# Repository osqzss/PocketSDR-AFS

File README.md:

# PocketSDR-AFS

PocketSDR-AFS is an enhanced version of Tomoji Takasu’s [PocketSDR v0.13](https://github.com/tomojitakasu/PocketSDR) designed to support the Augmented Forward Signal (AFS) for the Lunar Augmented Navigation Service (LANS).

LANS is the lunar counterpart to GNSS, developed to enable precise navigation and positioning for future lunar exploration missions. The AFS is a standardized signal structure for LANS. It is transmitted by multiple LunaNet Service Provider (LNSP) nodes, including NASA's Lunar Communications Relay and Navigation Systems (LCRNS), ESA's Moonlight Lunar Communications and Navigation Services (LCNS), and JAXA's Luna Navigation Satellite System (LNSS). The recommended standard for AFS can be found at NASA's [LunaNet Interoperability Specification](https://www.nasa.gov/directorates/somd/space-communications-navigation-program/lunanet-interoperability-specification/) site.

PocketSDR-AFS, in conjunction with a software-defined LANS AFS baseband simulator such as [LANS-AFS-SIM](https://github.com/osqzss/LANS-AFS-SIM), offers a flexible platform for validating LANS signal processing algorithms and evaluating lunar navigation performance.

## Build Instructions

### 1. Install Prerequisite Packages

```sh
sudo apt update
sudo apt install libusb-1.0-0-dev libfftw3-dev
```

### 2. Clone the Repository

```sh
git clone https://github.com/osqzss/PocketSDR-AFS.git
cd PocketSDR-AFS
```

### 3. Install External Library Source Trees

```sh
cd lib
chmod +x clone_lib.sh
./clone_lib.sh
```

### 4. Build the Libraries

```sh
cd build
make
make install
```

### 5. Build the `pocket_trk` Executable

```sh
cd ../../app/pocket_trk
make
```

## Usage

The `pocket_trk.sh` script in `app/pocket_trk` provides example command-line instructions for both offline and real-time testing:

- **Offline Testing:** Process 2-bit I/Q sample data generated by LANS-AFS-SIM.
- **Real-time Testing:** Use with the FE2CH frontend on a desktop PC or Raspberry Pi 5.

### Offline Testing Example

```sh
sudo ./pocket_trk.sh afssim_iq2.bin
```

### Real-time Testing Example (with FE2CH frontend)

```sh
sudo ./pocket_trk.sh
```

## Notes

- For development and testing purposes, the center frequency of the LANS AFS is set to 1575.42MHz. While the actual LANS AFS is transmitted in the S-band, this L-band configuration enables compatibility with the FE2CH frontend device, facilitating convenient real-time testing on desktop PCs or Raspberry Pi devices.
- To configure the receiver for S-band signal acquisition, edit the `src/pocket_sdr.h` file and comment out the `#define DEMO_L1` directive. This modification enables support for the S-band center frequency used by the actual LANS AFS broadcast.

## References

For additional details on the architecture and examples of offline and real-time test results, please refer to our publication:

Sobukawa, R., & Ebinuma, T. (2025). Open-Source Real-Time SDR Platform for Rapid Prototyping of LANS AFS Receiver. Aerospace, 12(7), 620. [https://doi.org/10.3390/aerospace12070620](https://www.mdpi.com/2226-4310/12/7/620)

What about the application of the Solomonoff induction
to the RF sensing of human brain?
https://en.wikipedia.org/wiki/Talk:Solomonoff%27s_theory_of_inductive_inference

If we assume that the algorithmic complexity
of neural processes is relatively small
(you could take a look at the Potapov monography
for some arguments)

As far as I know a lot of neural processes in human brain are electric (or electro-chemistry)
in nature. They have a little power and a small
frequency (~ 1-1000 Hz).
So they emit very low frequency radio waves.

You can detect those radio waves on
small antennas if the impedance of such antennas
is matched. This is basically the citation
from the book on electrodynamics.
I uploaded one such book on Twirpix site.

So you can create a lot of such receivers

microstrip filter to filter very high frequencies
impedance matched microstrip antenna
resistor for noise for oversampling
very fast comparator to sample signal
in a very large array on a chip using
standard CMOS or some sort of full-custom process
(maybe even with some new materials)

BeamForming and large arrays of digital correlators with sub-mm positioning accuracy
could be achived.

so it seems there is no theoretical
obstacles to implement some sort of
RF human brain sensing or even control
if you can implement reverse structure
with array of a large amount of RF amplifiers
with sub-mm beam forming accuracy

BTW I wrote that remark:
https://en.wikipedia.org/wiki/Talk:Solomonoff%27s_theory_of_inductive_inference

What about the application of the Solomonoff induction to the person to person information exchange?

It seems the minimum description length principle could be used to deduce minimum ethics. At least you can compare ethics by the length. What about the following question: how to shoot met-art girl in the dark underground? ~2026-24709-41 (talk) 16:43, 8 June 2026 (UTC)

at least we can ask a question: does russian met-art model from a pic want some money?
and what obstacles do that guess so hard?
why it is so hard to contact her directly?
she lose money, interesting person lose opportunity to make some photos.

also, it seems the economy without coordination primitives based on physics or mathematics
like gold or maybe Bitcoin or maybe some sort of other physical objects or processes
is just a chaos.
Economic calculation based on fiat money is impossible just from scientific methodology
https://en.wikipedia.org/wiki/Talk:Solomonoff%27s_theory_of_inductive_inference

It seems it is proof of the famous Mises calculation argument
https://mises.org/online-book/economic-calculation-socialist-commonwealth

https://transitional-writes.dreamwidth.org/44972.html
Kirill Abramovich
Samara, Russia

and the most important question:
what about the minimal ethics deduced from the MDL principle?
is it exist?

what was the obstacle between russian met-art girls and engineers?

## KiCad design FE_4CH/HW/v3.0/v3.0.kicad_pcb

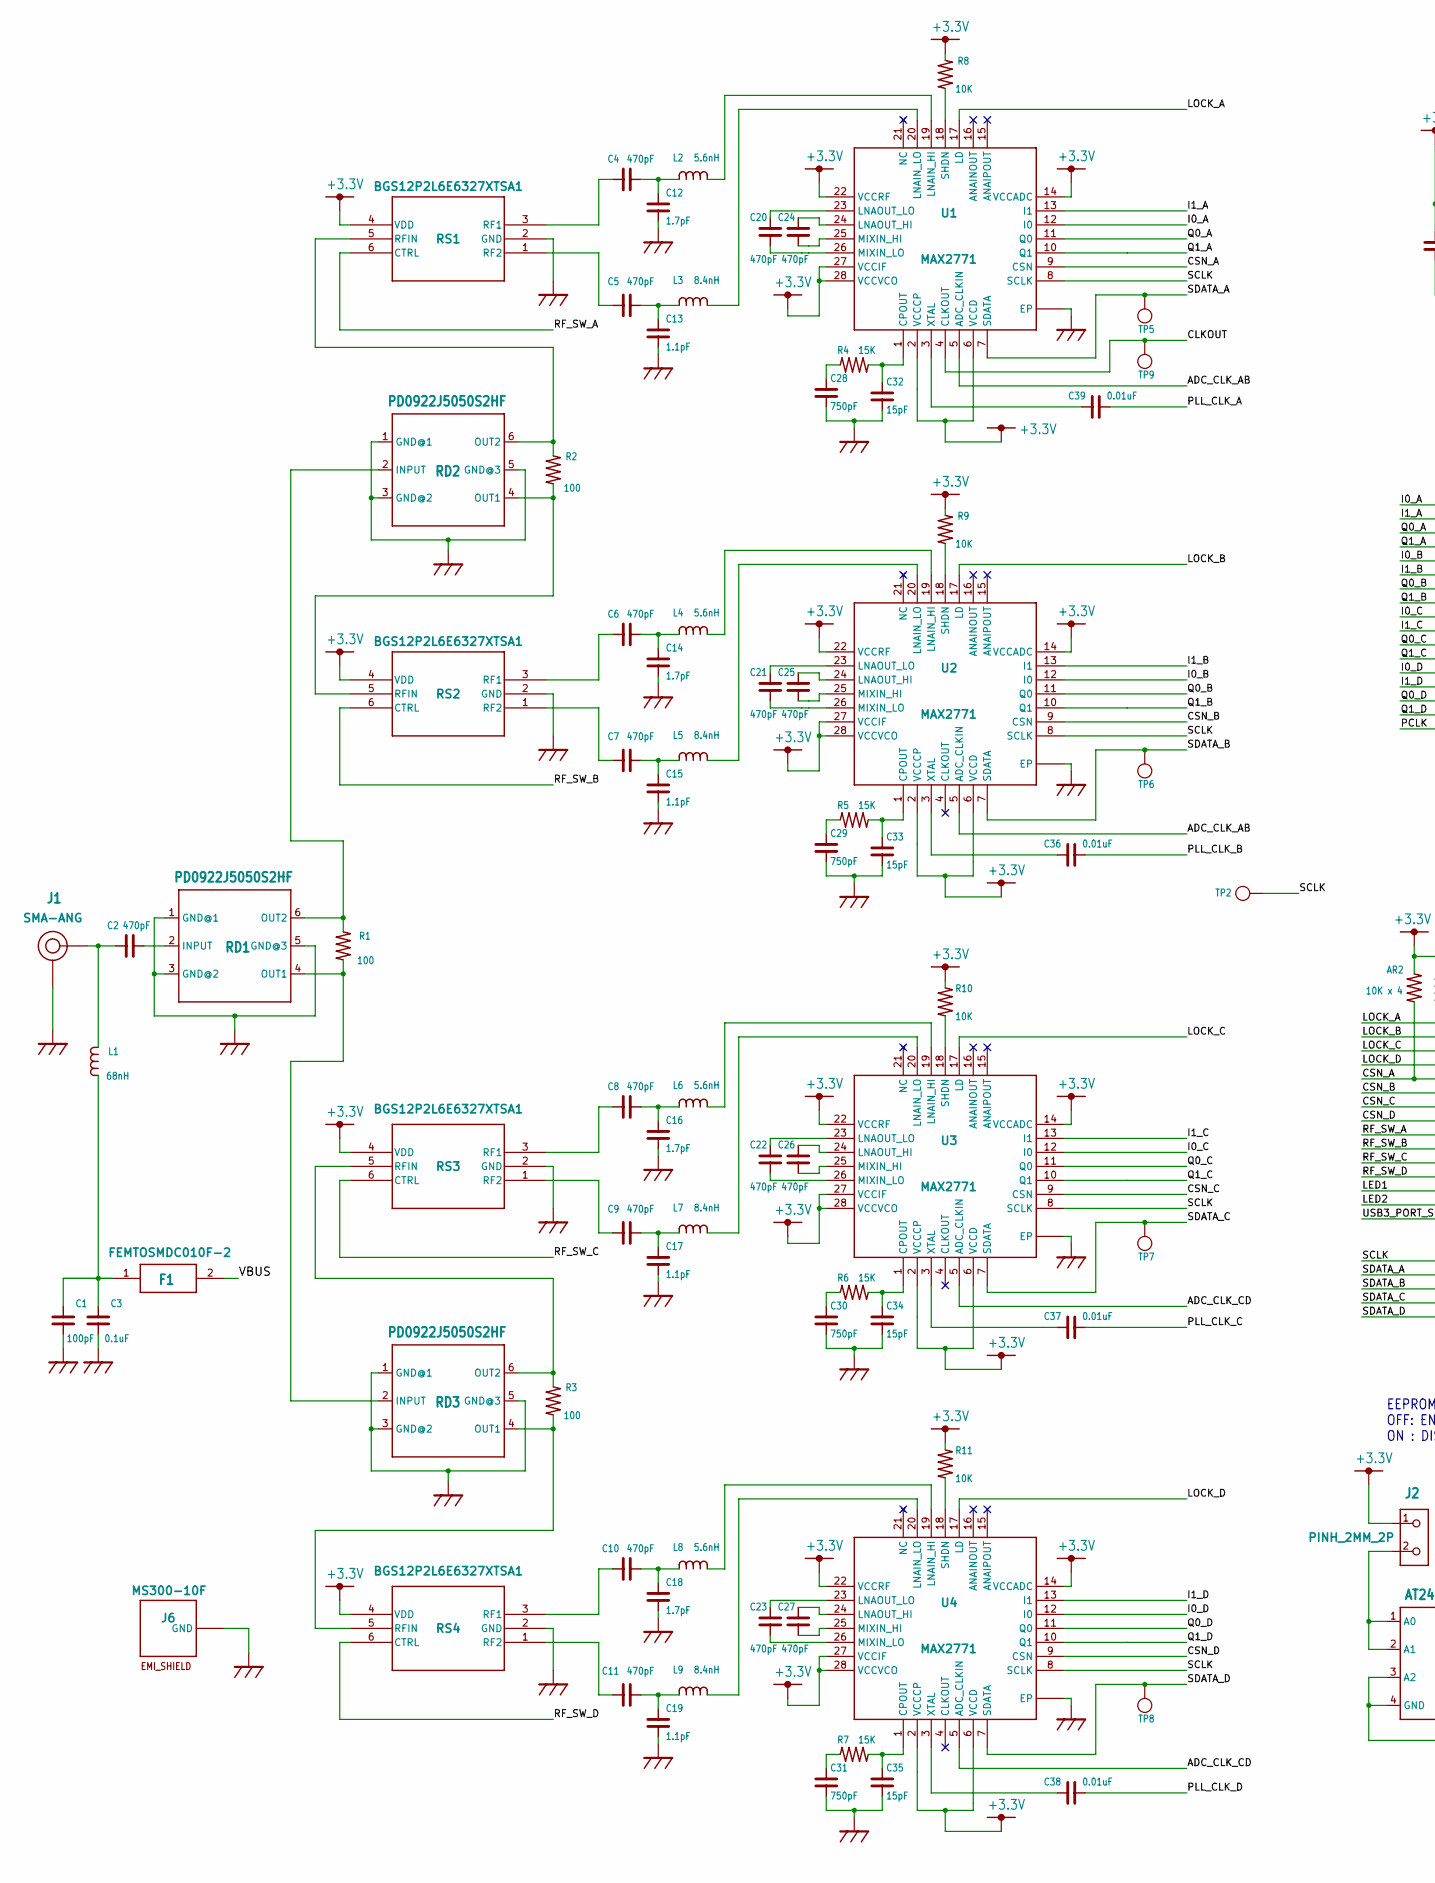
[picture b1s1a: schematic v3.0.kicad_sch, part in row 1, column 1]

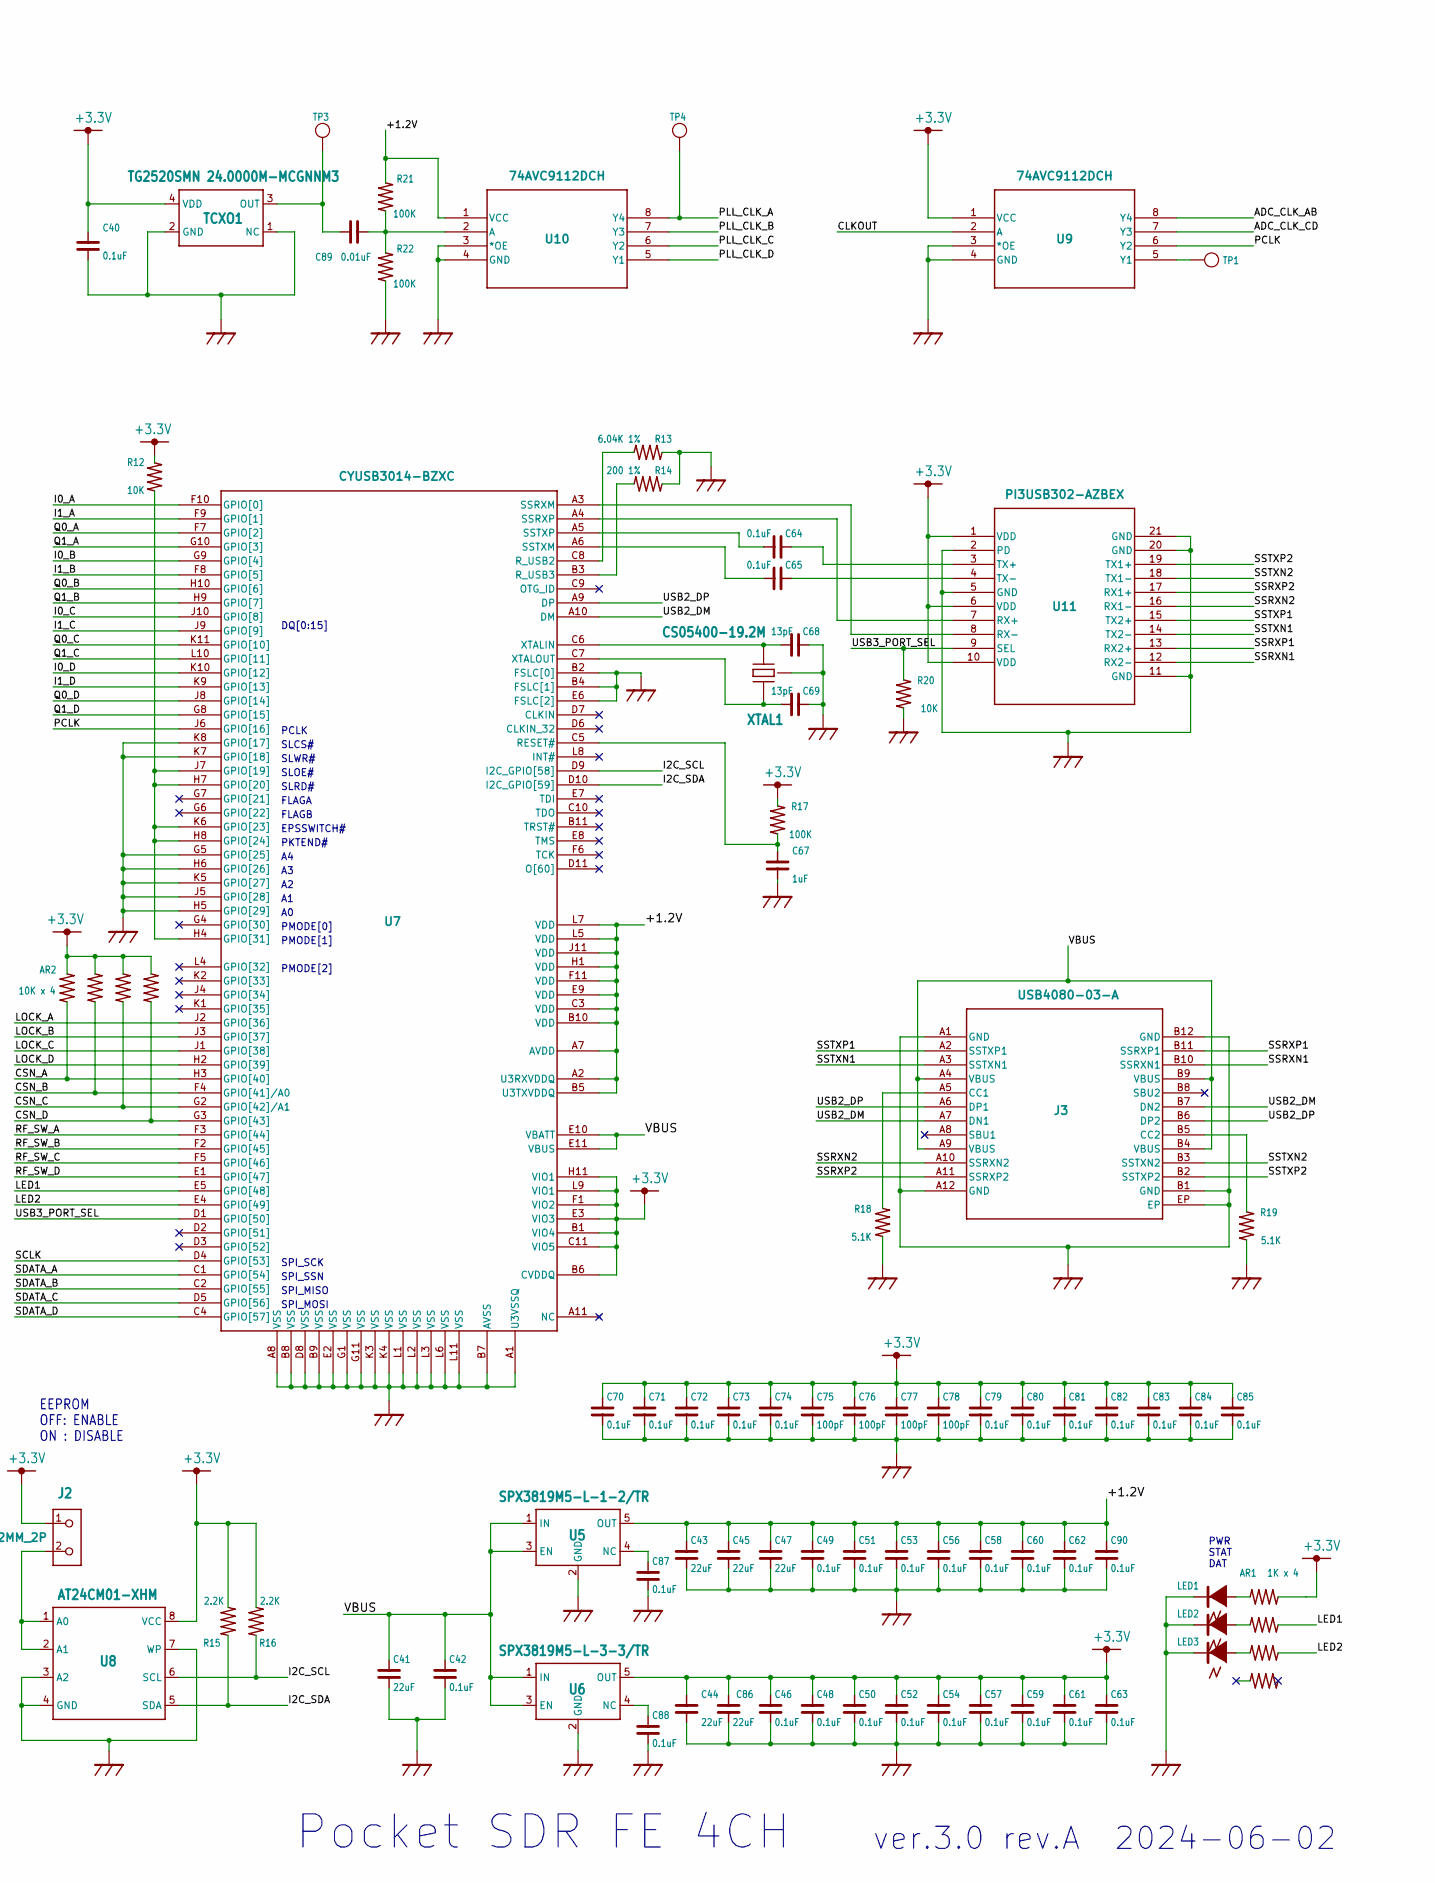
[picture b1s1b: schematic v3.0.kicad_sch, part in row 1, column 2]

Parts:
AR1: 1K x 4; EXB28V
AR2: 10K x 4; EXB28V
C1, C75, C76, C77, C78: 100pF; C1005
C2, C4, C5, C6, C7, C8, C9, C10, C11, C20, C21, C22, C23, C24, C25, C26, C27: 470pF; C1005
C3, C40, C42, C46, C48, C49, C50, C51, C52, C53, C54, C56, C57, C58, C59, C60, C61, C62, C63, C64, C65, C70, C71, C72, C73, C74, C79, C80, C81, C82, C83, C84, C85, C87, C88, C90: 0.1uF; C1005
C12, C14, C16, C18: 1.7pF; C1005
C13, C15, C17, C19: 1.1pF; C1005
C28, C29, C30, C31: 750pF; C1005
C32, C33, C34, C35: 15pF; C1005
C36, C37, C38, C39, C89: 0.01uF; C1005
C41, C43, C44, C45, C47, C86: 22uF; C1608
C67: 1uF; C1005
C68, C69: 13pF; C1005
F1: FEMTOSMDC010F-2; C1608
J1: SMA-ANG
J2: PINH_2MM_2P; PINH-2MM-2P
J3: USB4080-03-A; USB4080-03-A_GCT
J6: MS300-10F
L1: 68nH; C1608
L2, L4, L6, L8: 5.6nH; C1005
L3, L5, L7, L9: 8.4nH; C1005
LED1, LED2, LED3: LED1608; LED_1608
R1, R2, R3: 100; C1005
R4, R5, R6, R7: 15K; C1005
R8, R9, R10, R11, R12, R20: 10K; C1005
R13: 6.04K 1%; C1005
R14: 200 1%; C1005
R15, R16: 2.2K; C1005
R17, R21, R22: 100K; C1005
R18, R19: 5.1K; C1005
RD1, RD2, RD3: PD0922J5050S2HF; RF_DIV
RS1, RS2, RS3, RS4: BGS12P2L6E6327XTSA1; PG-TSLP-6-4_INF
TCXO1: TG2520SMN 24.0000M-MCGNNM3; TCXO
TP1, TP2, TP3, TP4, TP5, TP6, TP7, TP8, TP9: TP0.5
U1, U2, U3, U4: MAX2771; TQFN28
U5: SPX3819M5-L-1-2/TR; SOT23
U6: SPX3819M5-L-3-3/TR; SOT23
U7: CYUSB3014-BZXC; BGA-121
U8: AT24CM01-XHM; TSSOP_8P
U9, U10: 74AVC9112DCH; VSSOP8_SOT765-1_NEX
U11: PI3USB302-AZBEX; 20TQFN-ZB_PI3USB302-A_DIO
XTAL1: CS05400-19.2M; XTAL_SMD

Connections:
+3.3V: AR1.2, AR2.2, AR2.4, AR2.6, AR2.8, C40.1, C44.1, C46.1, C48.1, C50.1, C52.1, C54.1, C57.1, C59.1, C61.1, C63.1, C70.1, C71.1, C72.1, C73.1, C74.1, C75.1, C76.1, C77.1, C78.1, C79.1, C80.1, C81.1, C82.1, C83.1, C84.1, C85.1, C86.1, J2.1, R8.2, R9.2, R10.2, R11.2, R12.1, R15.2, R16.2, R17.2, RS1.4 (VDD), RS2.4 (VDD), RS3.4 (VDD), RS4.4 (VDD), TCXO1.4 (VDD), U1.2 (VCCCP), U1.6 (VCCD), U1.14 (VCCADC), U1.22 (VCCRF), U1.27 (VCCIF), U1.28 (VCCVCO), U2.2 (VCCCP), U2.6 (VCCD), U2.14 (VCCADC), U2.22 (VCCRF), U2.27 (VCCIF), U2.28 (VCCVCO), U3.2 (VCCCP), U3.6 (VCCD), U3.14 (VCCADC), U3.22 (VCCRF), U3.27 (VCCIF), U3.28 (VCCVCO), U4.2 (VCCCP), U4.6 (VCCD), U4.14 (VCCADC), U4.22 (VCCRF), U4.27 (VCCIF), U4.28 (VCCVCO), U6.5 (OUT), U7.B1 (VIO4), U7.B6 (CVDDQ), U7.C11 (VIO5), U7.E3 (VIO3), U7.F1 (VIO2), U7.H11 (VIO1), U7.L9 (VIO1), U8.8 (VCC), U9.1 (VCC), U11.1 (VDD), U11.6 (VDD), U11.10 (VDD)
/+1.2V: C43.1, C45.1, C47.1, C49.1, C51.1, C53.1, C56.1, C58.1, C60.1, C62.1, C90.1, R21.1, U5.5 (OUT), U7.A2 (U3RXVDDQ), U7.A7 (AVDD), U7.B5 (U3TXVDDQ), U7.B10 (VDD), U7.C3 (VDD), U7.E9 (VDD), U7.F11 (VDD), U7.H1 (VDD), U7.J11 (VDD), U7.L5 (VDD), U7.L7 (VDD), U10.1 (VCC)
/ADC_CLK_AB: U1.5 (ADC_CLKIN), U2.5 (ADC_CLKIN), U9.8 (Y4)
/ADC_CLK_CD: U3.5 (ADC_CLKIN), U4.5 (ADC_CLKIN), U9.7 (Y3)
/CLKOUT: TP9.1, U1.4 (CLKOUT), U9.2 (A)
/CSN_A: AR2.1, U1.9 (CSN), U7.H3 (GPIO[40])
/CSN_B: AR2.3, U2.9 (CSN), U7.F4 (GPIO[41]/A0)
/CSN_C: AR2.5, U3.9 (CSN), U7.G2 (GPIO[42]/A1)
/CSN_D: AR2.7, U4.9 (CSN), U7.G3 (GPIO[43])
/I0_A: U1.12 (I0), U7.F10 (GPIO[0])
/I0_B: U2.12 (I0), U7.G9 (GPIO[4])
/I0_C: U3.12 (I0), U7.J10 (GPIO[8])
/I0_D: U4.12 (I0), U7.K10 (GPIO[12])
/I1_A: U1.13 (I1), U7.F9 (GPIO[1])
/I1_B: U2.13 (I1), U7.F8 (GPIO[5])
/I1_C: U3.13 (I1), U7.J9 (GPIO[9])
/I1_D: U4.13 (I1), U7.K9 (GPIO[13])
/I2C_SCL: R16.1, U7.D9 (I2C_GPIO[58]), U8.6 (SCL)
/I2C_SDA: R15.1, U7.D10 (I2C_GPIO[59]), U8.5 (SDA)
/LED1: AR1.4, U7.E5 (GPIO[48])
/LED2: AR1.6, U7.E4 (GPIO[49])
/LOCK_A: U1.17 (LD), U7.J2 (GPIO[36])
/LOCK_B: U2.17 (LD), U7.J3 (GPIO[37])
/LOCK_C: U3.17 (LD), U7.J1 (GPIO[38])
/LOCK_D: U4.17 (LD), U7.H2 (GPIO[39])
/PCLK: U7.J6 (GPIO[16]), U9.6 (Y2)
/PLL_CLK_A: C39.1, TP4.1, U10.8 (Y4)
/PLL_CLK_B: C36.1, U10.7 (Y3)
/PLL_CLK_C: C37.1, U10.6 (Y2)
/PLL_CLK_D: C38.1, U10.5 (Y1)
/Q0_A: U1.11 (Q0), U7.F7 (GPIO[2])
/Q0_B: U2.11 (Q0), U7.H10 (GPIO[6])
/Q0_C: U3.11 (Q0), U7.K11 (GPIO[10])
/Q0_D: U4.11 (Q0), U7.J8 (GPIO[14])
/Q1_A: U1.10 (Q1), U7.G10 (GPIO[3])
/Q1_B: U2.10 (Q1), U7.H9 (GPIO[7])
/Q1_C: U3.10 (Q1), U7.L10 (GPIO[11])
/Q1_D: U4.10 (Q1), U7.G8 (GPIO[15])
/RF_SW_A: RS1.6 (CTRL), U7.F3 (GPIO[44])
/RF_SW_B: RS2.6 (CTRL), U7.F2 (GPIO[45])
/RF_SW_C: RS3.6 (CTRL), U7.F5 (GPIO[46])
/RF_SW_D: RS4.6 (CTRL), U7.E1 (GPIO[47])
/SCLK: TP2.1, U1.8 (SCLK), U2.8 (SCLK), U3.8 (SCLK), U4.8 (SCLK), U7.D4 (GPIO[53])
/SDATA_A: TP5.1, U1.7 (SDATA), U7.C1 (GPIO[54])
/SDATA_B: TP6.1, U2.7 (SDATA), U7.C2 (GPIO[55])
/SDATA_C: TP7.1, U3.7 (SDATA), U7.D5 (GPIO[56])
/SDATA_D: TP8.1, U4.7 (SDATA), U7.C4 (GPIO[57])
/SSRXN1: J3.B10 (SSRXN1), U11.12 (RX2-)
/SSRXN2: J3.A10 (SSRXN2), U11.16 (RX1-)
/SSRXP1: J3.B11 (SSRXP1), U11.13 (RX2+)
/SSRXP2: J3.A11 (SSRXP2), U11.17 (RX1+)
/SSTXN1: J3.A3 (SSTXN1), U11.14 (TX2-)
/SSTXN2: J3.B3 (SSTXN2), U11.18 (TX1-)
/SSTXP1: J3.A2 (SSTXP1), U11.15 (TX2+)
/SSTXP2: J3.B2 (SSTXP2), U11.19 (TX1+)
/USB2_DM: J3.A7 (DN1), J3.B7 (DN2), U7.A10 (DM)
/USB2_DP: J3.A6 (DP1), J3.B6 (DP2), U7.A9 (DP)
/USB3_PORT_SEL: R20.2, U7.D1 (GPIO[50]), U11.9 (SEL)
/VBUS: C41.1, C42.1, F1.2, J3.A4 (VBUS), J3.A9 (VBUS), J3.B4 (VBUS), J3.B9 (VBUS), U5.1 (IN), U5.3 (EN), U6.1 (IN), U6.3 (EN), U7.E10 (VBATT), U7.E11 (VBUS)
GND: C1.1, C3.1, C12.1, C13.1, C14.1, C15.1, C16.1, C17.1, C18.1, C19.1, C28.2, C29.2, C30.2, C31.2, C32.2, C33.2, C34.2, C35.2, C40.2, C41.2, C42.2, C43.2, C44.2, C45.2, C46.2, C47.2, C48.2, C49.2, C50.2, C51.2, C52.2, C53.2, C54.2, C56.2, C57.2, C58.2, C59.2, C60.2, C61.2, C62.2, C63.2, C67.2, C68.1, C69.1, C70.2, C71.2, C72.2, C73.2, C74.2, C75.2, C76.2, C77.2, C78.2, C79.2, C80.2, C81.2, C82.2, C83.2, C84.2, C85.2, C86.2, C87.2, C88.2, C90.2, J1.P2 (GND), J1.P3 (GND), J1.P4 (GND), J1.P5 (GND), J3.A1 (GND), J3.A12 (GND), J3.B1 (GND), J3.B12 (GND), J3.EP, J6.P1 (GND), LED1.2, LED2.2, LED3.2, R13.1, R14.1, R18.1, R19.1, R20.1, R22.2, RD1.1 (GND@1), RD1.3 (GND@2), RD1.5 (GND@3), RD2.1 (GND@1), RD2.3 (GND@2), RD2.5 (GND@3), RD3.1 (GND@1), RD3.3 (GND@2), RD3.5 (GND@3), RS1.2 (GND), RS2.2 (GND), RS3.2 (GND), RS4.2 (GND), TCXO1.1 (NC), TCXO1.2 (GND), U1.C1 (EP), U1.C2 (EP), U1.C3 (EP), U1.C4 (EP), U1.EP, U1.V1 (EP), U1.V2 (EP), U1.V3 (EP), U1.V4 (EP), U1.V5 (EP), U1.V6 (EP), U1.V7 (EP), U1.V8 (EP), U1.V9 (EP), U2.C1 (EP), U2.C2 (EP), U2.C3 (EP), U2.C4 (EP), U2.EP, U2.V1 (EP), U2.V2 (EP), U2.V3 (EP), U2.V4 (EP), U2.V5 (EP), U2.V6 (EP), U2.V7 (EP), U2.V8 (EP), U2.V9 (EP), U3.C1 (EP), U3.C2 (EP), U3.C3 (EP), U3.C4 (EP), U3.EP, U3.V1 (EP), U3.V2 (EP), U3.V3 (EP), U3.V4 (EP), U3.V5 (EP), U3.V6 (EP), U3.V7 (EP), U3.V8 (EP), U3.V9 (EP), U4.C1 (EP), U4.C2 (EP), U4.C3 (EP), U4.C4 (EP), U4.EP, U4.V1 (EP), U4.V2 (EP), U4.V3 (EP), U4.V4 (EP), U4.V5 (EP), U4.V6 (EP), U4.V7 (EP), U4.V8 (EP), U4.V9 (EP), U5.2 (GND), U6.2 (GND), U7.A1 (U3VSSQ), U7.A8 (VSS), U7.B2 (FSLC[0]), U7.B4 (FSLC[1]), U7.B7 (AVSS), U7.B8 (VSS), U7.B9 (VSS), U7.D8 (VSS), U7.E2 (VSS), U7.E6 (FSLC[2]), U7.G1 (VSS), U7.G5 (GPIO[25]), U7.G11 (VSS), U7.H5 (GPIO[29]), U7.H6 (GPIO[26]), U7.J5 (GPIO[28])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
unnamed: AR1.1, LED1.1 (+)
unnamed: AR1.3, LED2.1 (+)
unnamed: AR1.5, LED3.1 (+)
unnamed: C1.2, C3.2, F1.1, L1.1
unnamed: C2.1, J1.P1 (RF), L1.2
unnamed: J2.2, U8.1 (A0), U8.2 (A1)
unnamed: J3.A5 (CC1), R18.2
unnamed: J3.B5 (CC2), R19.2
unnamed: C4.2, C12.2, L2.1
unnamed: L2.2, U1.19 (LNAIN_HI)
unnamed: C5.2, C13.2, L3.1
unnamed: L3.2, U1.20 (LNAIN_LO)
unnamed: C6.2, C14.2, L4.1
unnamed: L4.2, U2.19 (LNAIN_HI)
unnamed: C7.2, C15.2, L5.1
unnamed: L5.2, U2.20 (LNAIN_LO)
unnamed: C8.2, C16.2, L6.1
unnamed: L6.2, U3.19 (LNAIN_HI)
unnamed: C9.2, C17.2, L7.1
unnamed: L7.2, U3.20 (LNAIN_LO)
unnamed: C10.2, C18.2, L8.1
unnamed: L8.2, U4.19 (LNAIN_HI)
unnamed: C11.2, C19.2, L9.1
unnamed: L9.2, U4.20 (LNAIN_LO)
unnamed: R1.1, RD1.4 (OUT1), RD3.2 (INPUT)
unnamed: R1.2, RD1.6 (OUT2), RD2.2 (INPUT)
unnamed: R2.1, RD2.4 (OUT1), RS2.5 (RFIN)
unnamed: R2.2, RD2.6 (OUT2), RS1.5 (RFIN)
unnamed: R3.1, RD3.4 (OUT1), RS4.5 (RFIN)
unnamed: R3.2, RD3.6 (OUT2), RS3.5 (RFIN)
unnamed: C28.1, R4.1
unnamed: C32.1, R4.2, U1.1 (CPOUT)
unnamed: C29.1, R5.1
unnamed: C33.1, R5.2, U2.1 (CPOUT)
unnamed: C30.1, R6.1
unnamed: C34.1, R6.2, U3.1 (CPOUT)
unnamed: C31.1, R7.1
unnamed: C35.1, R7.2, U4.1 (CPOUT)
unnamed: R8.1, U1.18 (SHDN)
unnamed: R9.1, U2.18 (SHDN)
unnamed: R10.1, U3.18 (SHDN)
unnamed: R11.1, U4.18 (SHDN)
unnamed: R12.2, U7.H4 (GPIO[31]), U7.H7 (GPIO[20]), U7.H8 (GPIO[24]), U7.J7 (GPIO[19]), U7.K6 (GPIO[23])
unnamed: R13.2, U7.C8 (R_USB2)
unnamed: R14.2, U7.B3 (R_USB3)
unnamed: C67.1, R17.1, U7.C5 (RESET#)
unnamed: C89.2, R21.2, R22.1, U10.2 (A)
unnamed: C2.2, RD1.2 (INPUT)
unnamed: C4.1, RS1.3 (RF1)
unnamed: C5.1, RS1.1 (RF2)
unnamed: C6.1, RS2.3 (RF1)
unnamed: C7.1, RS2.1 (RF2)
unnamed: C8.1, RS3.3 (RF1)
unnamed: C9.1, RS3.1 (RF2)
unnamed: C10.1, RS4.3 (RF1)
unnamed: C11.1, RS4.1 (RF2)
unnamed: C89.1, TCXO1.3 (OUT), TP3.1
unnamed: C24.1, U1.24 (LNAOUT_HI)
unnamed: C20.1, U1.23 (LNAOUT_LO)
unnamed: C24.2, U1.25 (MIXIN_HI)
unnamed: C20.2, U1.26 (MIXIN_LO)
unnamed: C39.2, U1.3 (XTAL)
unnamed: C25.1, U2.24 (LNAOUT_HI)
unnamed: C21.1, U2.23 (LNAOUT_LO)
unnamed: C25.2, U2.25 (MIXIN_HI)
unnamed: C21.2, U2.26 (MIXIN_LO)
unnamed: C36.2, U2.3 (XTAL)
unnamed: C26.1, U3.24 (LNAOUT_HI)
unnamed: C22.1, U3.23 (LNAOUT_LO)
unnamed: C26.2, U3.25 (MIXIN_HI)
unnamed: C22.2, U3.26 (MIXIN_LO)
unnamed: C37.2, U3.3 (XTAL)
unnamed: C27.1, U4.24 (LNAOUT_HI)
unnamed: C23.1, U4.23 (LNAOUT_LO)
unnamed: C27.2, U4.25 (MIXIN_HI)
unnamed: C23.2, U4.26 (MIXIN_LO)
unnamed: C38.2, U4.3 (XTAL)
unnamed: C87.1, U5.4 (NC)
unnamed: C88.1, U6.4 (NC)
unnamed: C65.2, U7.A6 (SSTXM)
unnamed: C64.2, U7.A5 (SSTXP)
unnamed: C68.2, U7.C6 (XTALIN), XTAL1.P1 (XTAL1)
unnamed: C69.2, U7.C7 (XTALOUT), XTAL1.P3 (XTAL2)
unnamed: TP1.1, U9.5 (Y1)
unnamed: U7.A4 (SSRXP), U11.7 (RX+)
unnamed: U7.A3 (SSRXM), U11.8 (RX-)
unnamed: C64.1, U11.3 (TX+)
unnamed: C65.1, U11.4 (TX-)

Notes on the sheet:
PCLK
EPSSWITCH#
SPI_SSN
PMODE[1]
DQ[0:15]
Pocket SDR FE 4CH
PMODE[0]
EEPROM OFF: ENABLE ON : DISABLE
SPI_SCK
SPI_MOSI
SLRD#
SLOE#
SLCS#
PMODE[2]
PWR STAT DAT
SLWR#
PKTEND#
ver.3.0 rev.A 2024-06-02
SPI_MISO
FLAGA
FLAGB

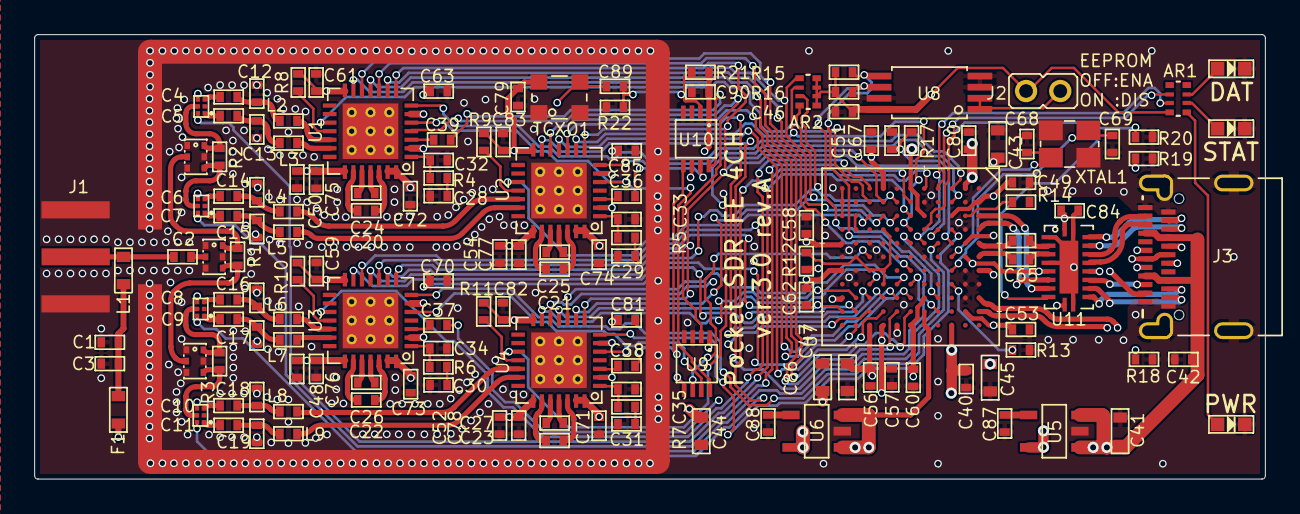
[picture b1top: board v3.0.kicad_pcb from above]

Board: 4 copper layers, 72.0 x 26.0 mm, 158 parts (0 on the bottom side), 148 nets.

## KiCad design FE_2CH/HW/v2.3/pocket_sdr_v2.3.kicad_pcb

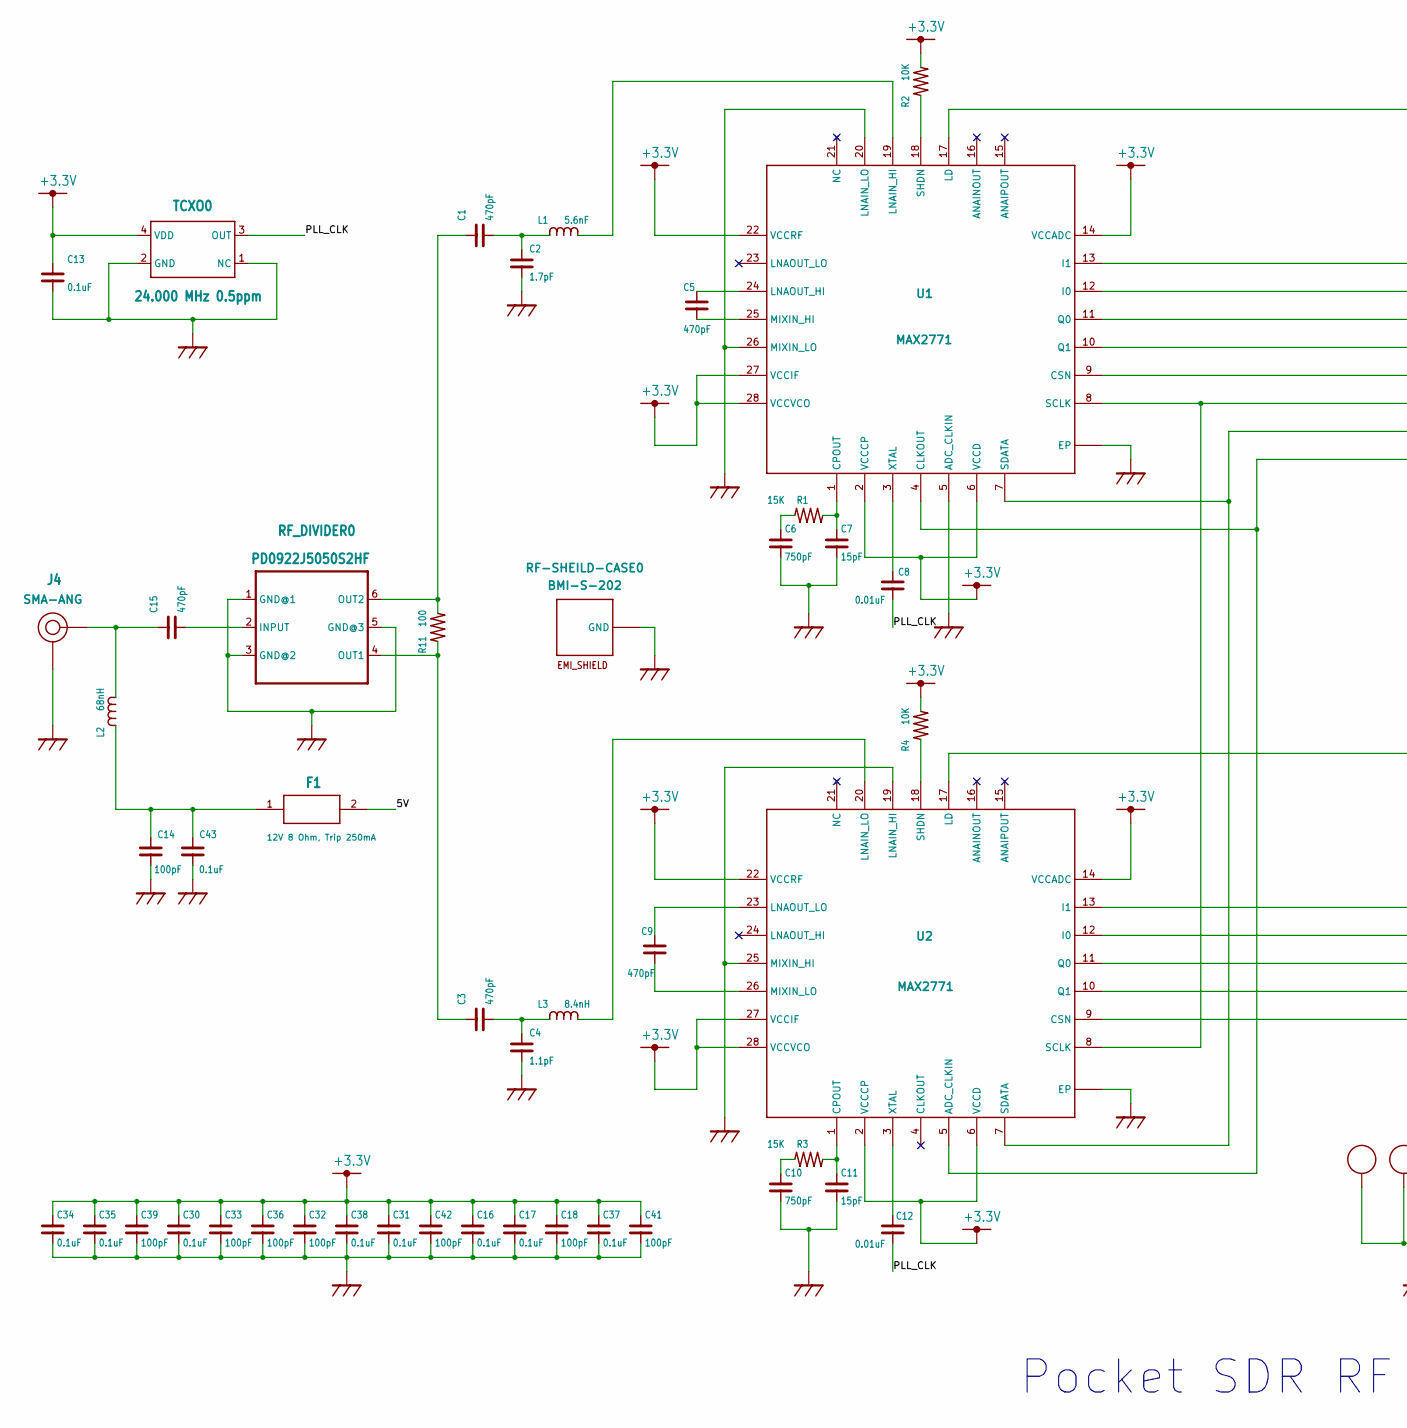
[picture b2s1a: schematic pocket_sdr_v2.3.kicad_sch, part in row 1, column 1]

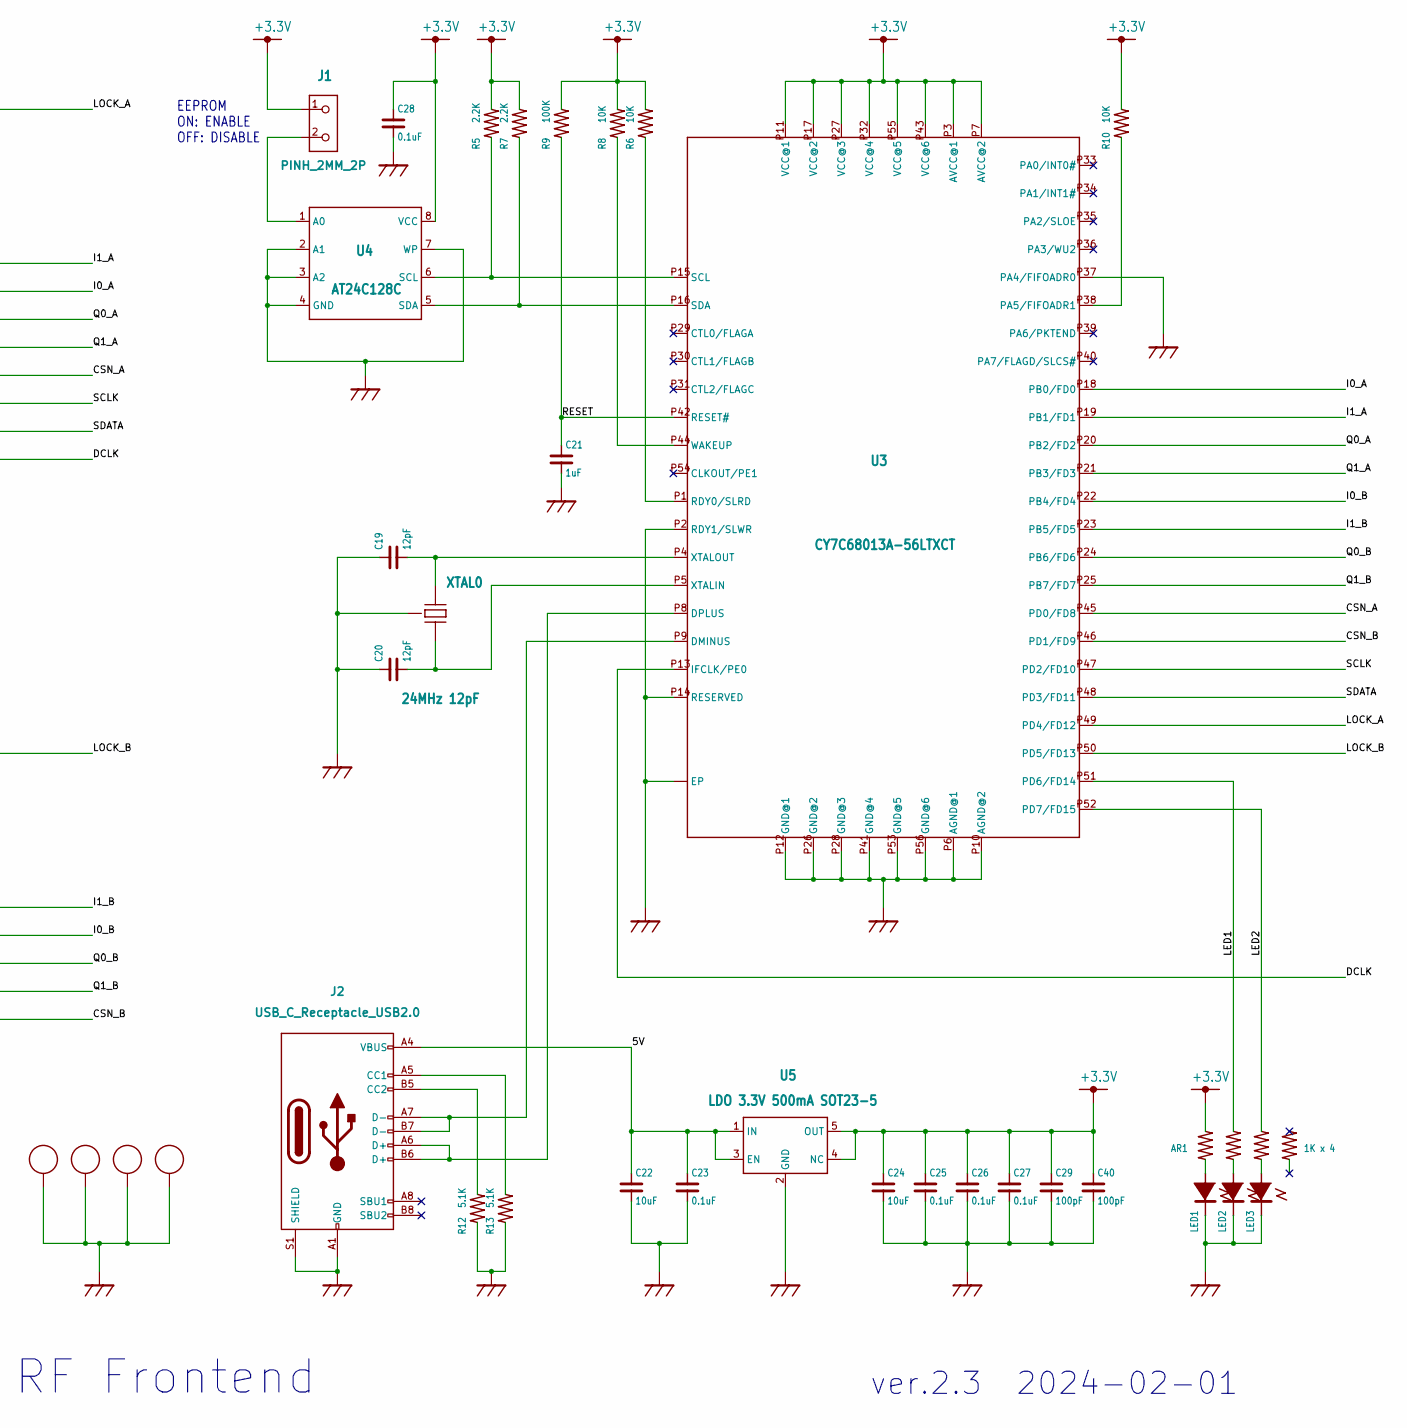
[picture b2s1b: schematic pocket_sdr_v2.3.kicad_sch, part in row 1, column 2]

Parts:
AR1: 1K x 4; EXB28V
C1, C3, C5, C9, C15: 470pF; C1005
C2: 1.7pF; C1005
C4: 1.1pF; C1005
C6, C10: 750pF; C1005
C7, C11: 15pF; C1005
C8, C12: 0.01uF; C1005
C13, C16, C17, C23, C25, C26, C27, C28, C30, C31, C34, C35, C37, C38, C43: 0.1uF; C1005
C14, C18, C29, C32, C33, C36, C39, C40, C41, C42: 100pF; C1005
C19, C20: 12pF; C1005
C21: 1uF; C1005
C22, C24: 10uF; C3225
F1: 12V 8 Ohm, Trip 250mA; C1608
J1: PINH_2MM_2P; PINH-2MM-2P
J2: USB_C_Receptacle_USB2.0
J4: SMA-ANG
L1: 5.6nF; C1608
L2: 68nH; C1608
L3: 8.4nH; C1608
LED1, LED2, LED3: LED1608; LED_1608
R1, R3: 15K; C1005
R2, R4, R6, R8, R10: 10K; C1005
R5, R7: 2.2K; C1005
R9: 100K; C1005
R11: 100; C1005
R12, R13: 5.1K; C1005
RF-SHEILD-CASE0: BMI-S-202
RF_DIVIDER0: PD0922J5050S2HF; RF_DIV
TCXO0: 24.000 MHz 0.5ppm; TCXO
U1, U2: MAX2771; TQFN28
U3: CY7C68013A-56LTXCT; QFN56
U4: AT24C128C; TSSOP_8P
U5: LDO 3.3V 500mA SOT23-5; SOT23
XTAL0: 24MHz 12pF; XTAL_SMD

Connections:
+3.3V: AR1.2, C13.1, C16.1, C17.1, C18.1, C24.P$1 (1), C25.1, C26.1, C27.1, C28.1, C29.1, C30.1, C31.1, C32.1, C33.1, C34.1, C35.1, C36.1, C37.1, C38.1, C39.1, C40.1, C41.1, C42.1, J1.1, R2.2, R4.2, R5.2, R6.2, R7.2, R8.2, R9.2, R10.2, TCXO0.4 (VDD), U1.2 (VCCCP), U1.6 (VCCD), U1.14 (VCCADC), U1.22 (VCCRF), U1.27 (VCCIF), U1.28 (VCCVCO), U2.2 (VCCCP), U2.6 (VCCD), U2.14 (VCCADC), U2.22 (VCCRF), U2.27 (VCCIF), U2.28 (VCCVCO), U3.P3 (AVCC@1), U3.P7 (AVCC@2), U3.P11 (VCC@1), U3.P17 (VCC@2), U3.P27 (VCC@3), U3.P32 (VCC@4), U3.P43 (VCC@6), U3.P55 (VCC@5), U4.8 (VCC), U5.4 (NC), U5.5 (OUT)
/5V: C22.P$1 (1), C23.1, F1.2, J2.A4 (VBUS), J2.A9 (VBUS), J2.B4 (VBUS), J2.B9 (VBUS), U5.1 (IN), U5.3 (EN)
/CSN_A: U1.9 (CSN), U3.P45 (PD0/FD8)
/CSN_B: U2.9 (CSN), U3.P46 (PD1/FD9)
/DCLK: U1.4 (CLKOUT), U2.5 (ADC_CLKIN), U3.P13 (IFCLK/PE0)
/I0_A: U1.12 (I0), U3.P18 (PB0/FD0)
/I0_B: U2.12 (I0), U3.P22 (PB4/FD4)
/I1_A: U1.13 (I1), U3.P19 (PB1/FD1)
/I1_B: U2.13 (I1), U3.P23 (PB5/FD5)
/LED1: AR1.4, U3.P51 (PD6/FD14)
/LED2: AR1.6, U3.P52 (PD7/FD15)
/LOCK_A: U1.17 (LD), U3.P49 (PD4/FD12)
/LOCK_B: U2.17 (LD), U3.P50 (PD5/FD13)
/PLL_CLK: C8.1, C12.1, TCXO0.3 (OUT)
/Q0_A: U1.11 (Q0), U3.P20 (PB2/FD2)
/Q0_B: U2.11 (Q0), U3.P24 (PB6/FD6)
/Q1_A: U1.10 (Q1), U3.P21 (PB3/FD3)
/Q1_B: U2.10 (Q1), U3.P25 (PB7/FD7)
/RESET: C21.1, R9.1, U3.P42 (RESET#)
/SCLK: U1.8 (SCLK), U2.8 (SCLK), U3.P47 (PD2/FD10)
/SDATA: U1.7 (SDATA), U2.7 (SDATA), U3.P48 (PD3/FD11)
GND: C2.1, C4.2, C6.2, C7.2, C10.2, C11.2, C13.2, C14.1, C16.2, C17.2, C18.2, C19.1, C20.1, C21.2, C22.P$2 (2), C23.2, C24.P$2 (2), C25.2, C26.2, C27.2, C28.2, C29.2, C30.2, C31.2, C32.2, C33.2, C34.2, C35.2, C36.2, C37.2, C38.2, C39.2, C40.2, C41.2, C42.2, C43.1, J2.A1 (GND), J2.A12 (GND), J2.B1 (GND), J2.B12 (GND), J2.S1 (SHIELD), J4.P2 (GND), J4.P3 (GND), J4.P4 (GND), J4.P5 (GND), LED1.2, LED2.2, LED3.2, R12.1, R13.1, RF-SHEILD-CASE0.P1 (GND), RF-SHEILD-CASE0.P2 (GND), RF-SHEILD-CASE0.P3 (GND), RF-SHEILD-CASE0.P4 (GND), RF-SHEILD-CASE0.P5 (GND), RF-SHEILD-CASE0.P6 (GND), RF-SHEILD-CASE0.P7 (GND), RF-SHEILD-CASE0.P8 (GND), RF-SHEILD-CASE0.P9 (GND), RF-SHEILD-CASE0.P10 (GND), RF-SHEILD-CASE0.P11 (GND), RF-SHEILD-CASE0.P12 (GND), RF_DIVIDER0.1 (GND@1), RF_DIVIDER0.3 (GND@2), RF_DIVIDER0.5 (GND@3), TCXO0.1 (NC), TCXO0.2 (GND), U1.5 (ADC_CLKIN), U1.20 (LNAIN_LO), U1.26 (MIXIN_LO), U1.C1 (EP), U1.C2 (EP), U1.C3 (EP), U1.C4 (EP), U1.EP, U1.V1 (EP), U1.V2 (EP), U1.V3 (EP), U1.V4 (EP), U1.V5 (EP), U1.V6 (EP), U1.V7 (EP), U1.V8 (EP), U1.V9 (EP), U2.19 (LNAIN_HI), U2.25 (MIXIN_HI), U2.C1 (EP), U2.C2 (EP), U2.C3 (EP), U2.C4 (EP), U2.EP, U2.V1 (EP), U2.V2 (EP), U2.V3 (EP), U2.V4 (EP), U2.V5 (EP), U2.V6 (EP), U2.V7 (EP), U2.V8 (EP), U2.V9 (EP), U3.EP1 (EP), U3.EP2 (EP), U3.EP3 (EP), U3.EP4 (EP), U3.EP5 (EP), U3.P2 (RDY1/SLWR), U3.P6 (AGND@1), U3.P10 (AGND@2), U3.P12 (GND@1), U3.P14 (RESERVED), U3.P26 (GND@2), U3.P28 (GND@3), U3.P37 (PA4/FIFOADR0), U3.P41 (GND@4), U3.P53 (GND@5), U3.P56 (GND@6), U3.P$1 (EP), U3.P$2 (EP), U3.P$3 (EP), U3.P$4 (EP), U3.P$5 (EP), U3.P$6 (EP), U3.P$7 (EP), U3.P$8 (EP), U3.P$9 (EP), U3.P$10 (EP), U3.P$11 (EP), U3.P$12 (EP), U3.P$13 (EP), U3.P$14 (EP), U3.P$15 (EP), U3.P$16 (EP), U3.P$17 (EP), U3.P$18 (EP), U3.P$19 (EP), U3.P$20 (EP), U4.2 (A1), U4.3 (A2), U4.4 (GND), U4.7 (WP), U5.2 (GND), XTAL0.P2 (GND), XTAL0.P4 (GND)
unnamed: AR1.1, LED1.1 (+)
unnamed: AR1.3, LED2.1 (+)
unnamed: AR1.5, LED3.1 (+)
unnamed: C14.2, C43.2, F1.1, L2.1
unnamed: J1.2, U4.1 (A0)
unnamed: J2.A5 (CC1), R13.2
unnamed: J2.B5 (CC2), R12.2
unnamed: C15.1, J4.P1 (RF), L2.2
unnamed: C1.2, C2.2, L1.1
unnamed: L1.2, U1.19 (LNAIN_HI)
unnamed: C3.2, C4.1, L3.1
unnamed: L3.2, U2.20 (LNAIN_LO)
unnamed: C6.1, R1.1
unnamed: C7.1, R1.2, U1.1 (CPOUT)
unnamed: R2.1, U1.18 (SHDN)
unnamed: C10.1, R3.1
unnamed: C11.1, R3.2, U2.1 (CPOUT)
unnamed: R4.1, U2.18 (SHDN)
unnamed: R5.1, U3.P15 (SCL), U4.6 (SCL)
unnamed: R6.1, U3.P1 (RDY0/SLRD)
unnamed: R7.1, U3.P16 (SDA), U4.5 (SDA)
unnamed: R8.1, U3.P44 (WAKEUP)
unnamed: R10.1, U3.P38 (PA5/FIFOADR1)
unnamed: C3.1, R11.1, RF_DIVIDER0.4 (OUT1)
unnamed: C1.1, R11.2, RF_DIVIDER0.6 (OUT2)
unnamed: C15.2, RF_DIVIDER0.2 (INPUT)
unnamed: C5.1, U1.24 (LNAOUT_HI)
unnamed: C5.2, U1.25 (MIXIN_HI)
unnamed: C8.2, U1.3 (XTAL)
unnamed: C9.1, U2.23 (LNAOUT_LO)
unnamed: C9.2, U2.26 (MIXIN_LO)
unnamed: C12.2, U2.3 (XTAL)
unnamed: J2.A7 (D-), J2.B7 (D-), U3.P9 (DMINUS)
unnamed: J2.A6 (D+), J2.B6 (D+), U3.P8 (DPLUS)
unnamed: C20.2, U3.P5 (XTALIN), XTAL0.P3 (XTAL2)
unnamed: C19.2, U3.P4 (XTALOUT), XTAL0.P1 (XTAL1)

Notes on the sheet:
Pocket SDR RF Frontend
EEPROM ON: ENABLE OFF: DISABLE
ver.2.3 2024-02-01

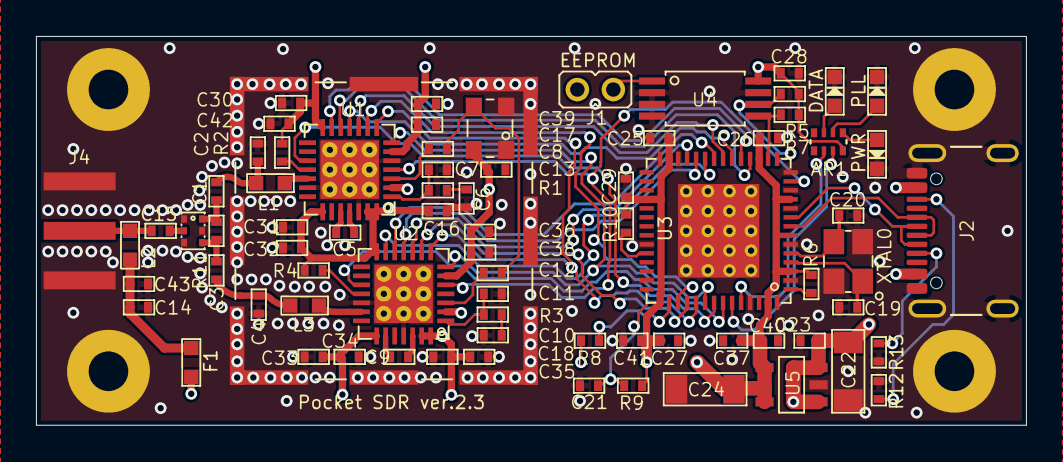
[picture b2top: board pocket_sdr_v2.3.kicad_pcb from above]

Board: 4 copper layers, 55.0 x 21.6 mm, 76 parts (0 on the bottom side), 58 nets.

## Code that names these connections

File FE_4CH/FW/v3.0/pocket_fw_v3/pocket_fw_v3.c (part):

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#ifndef F_TCXO
#define F_TCXO       24000      // TCXO frequency (kHz)
#endif
#define LOCK_A       36         // FX3 GPIO(36) <-- MAX2771 CH1 LD  (0x24)
#define LOCK_B       37         // FX3 GPIO(37) <-- MAX2771 CH2 LD  (0x25)
#define LOCK_C       38         // FX3 GPIO(38) <-- MAX2771 CH3 LD  (0x26)
#define LOCK_D       39         // FX3 GPIO(39) <-- MAX2771 CH4 LD  (0x27)
#define CSN_A        40         // FX3 GPIO(40) --> MAX2771 CH1 CSN (0x28)
#define CSN_B        41         // FX3 GPIO(41) --> MAX2771 CH2 CSN (0x29)
#define CSN_C        42         // FX3 GPIO(42) --> MAX2771 CH3 CSN (0x2A)
#define CSN_D        43         // FX3 GPIO(43) --> MAX2771 CH4 CSN (0x2B)
#define RF_SW_A      44         // FX3 GPIO(44) --> RF_SW CH1       (0x2C)
#define RF_SW_B      45         // FX3 GPIO(45) --> RF_SW CH2       (0x2D)
#define RF_SW_C      46         // FX3 GPIO(46) --> RF_SW CH3       (0x2E)
#define RF_SW_D      47         // FX3 GPIO(47) --> RF_SW CH4       (0x2F)
#define LED1         48         // FX3 GPIO(48) --> LED1            (0x30)
#define LED2         49         // FX3 GPIO(49) --> LED2            (0x31)
#define USB3_PORT_SEL 50        // FX3 GPIO(50) --> USB3_PORT_SEL   (0x32)
#define SCLK         53         // FX3 GPIO(53) --> MAX2771 SCLK    (0x35)
#ifdef REV_A
#define SDATA_A      54         // FX3 GPIO(54) <-> MAX2771 CH1 SDATA (0x36)
#define SDATA_B      55         // FX3 GPIO(55) <-> MAX2771 CH2 SDATA (0x37)
#define SDATA_C      56         // FX3 GPIO(56) <-> MAX2771 CH3 SDATA (0x38)
#define SDATA_D      57         // FX3 GPIO(57) <-> MAX2771 CH4 SDATA (0x39)
#else
#define SDATA        55         // FX3 GPIO(55) <-> MAX2771 SDATA   (0x37)
#endif
#define SCLK_CYC     10         // SPI SCLK delay

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static uint8_t EP0BUFF[128] __attribute__ ((aligned (32))); // EP0 data buffer

// IO ports definitions
static const uint8_t port_out[] = {RF_SW_A, RF_SW_B, RF_SW_C, RF_SW_D,
    USB3_PORT_SEL, SCLK, CSN_A, CSN_B, CSN_C, CSN_D, LED1, LED2, 0};
#ifdef REV_A
static const uint8_t port_inp[] = {LOCK_A, LOCK_B, LOCK_C, LOCK_D, SDATA_A,
    SDATA_B, SDATA_C, SDATA_D, 0};
static const uint8_t port_sdata[] = {SDATA_A, SDATA_B, SDATA_C, SDATA_D};
#else
static const uint8_t port_inp[] = {LOCK_A, LOCK_B, LOCK_C, LOCK_D, SDATA, 0};
static const uint8_t port_sdata[] = {SDATA, SDATA, SDATA, SDATA};
#endif
static const uint8_t port_csn[MAX_CH] = {CSN_A, CSN_B, CSN_C, CSN_D};
static const uint8_t port_rsw[MAX_CH] = {RF_SW_A, RF_SW_B, RF_SW_C, RF_SW_D};

// default MAX2771 settings
static const uint32_t reg_default[MAX_CH][MAX_ADDR] = {
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{
    // initialize P-port I/F block
    CyU3PPibClock_t pclk = {0};
    pclk.clkDiv = 2;
    pclk.clkSrc = CY_U3P_SYS_CLK;
    if (CyU3PPibInit(CyTrue, &pclk)) return 0;
    
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
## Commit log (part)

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2025-06-05 Remove executables
2025-06-14 Support LANS AFS
2026-05-10 Disable DEMO_L1
2026-05-10 Add .gitignore
2026-06-09 Solomonoff inductive inference for the GPS engineers
    https://transitional-writes.dreamwidth.org/44972.html
